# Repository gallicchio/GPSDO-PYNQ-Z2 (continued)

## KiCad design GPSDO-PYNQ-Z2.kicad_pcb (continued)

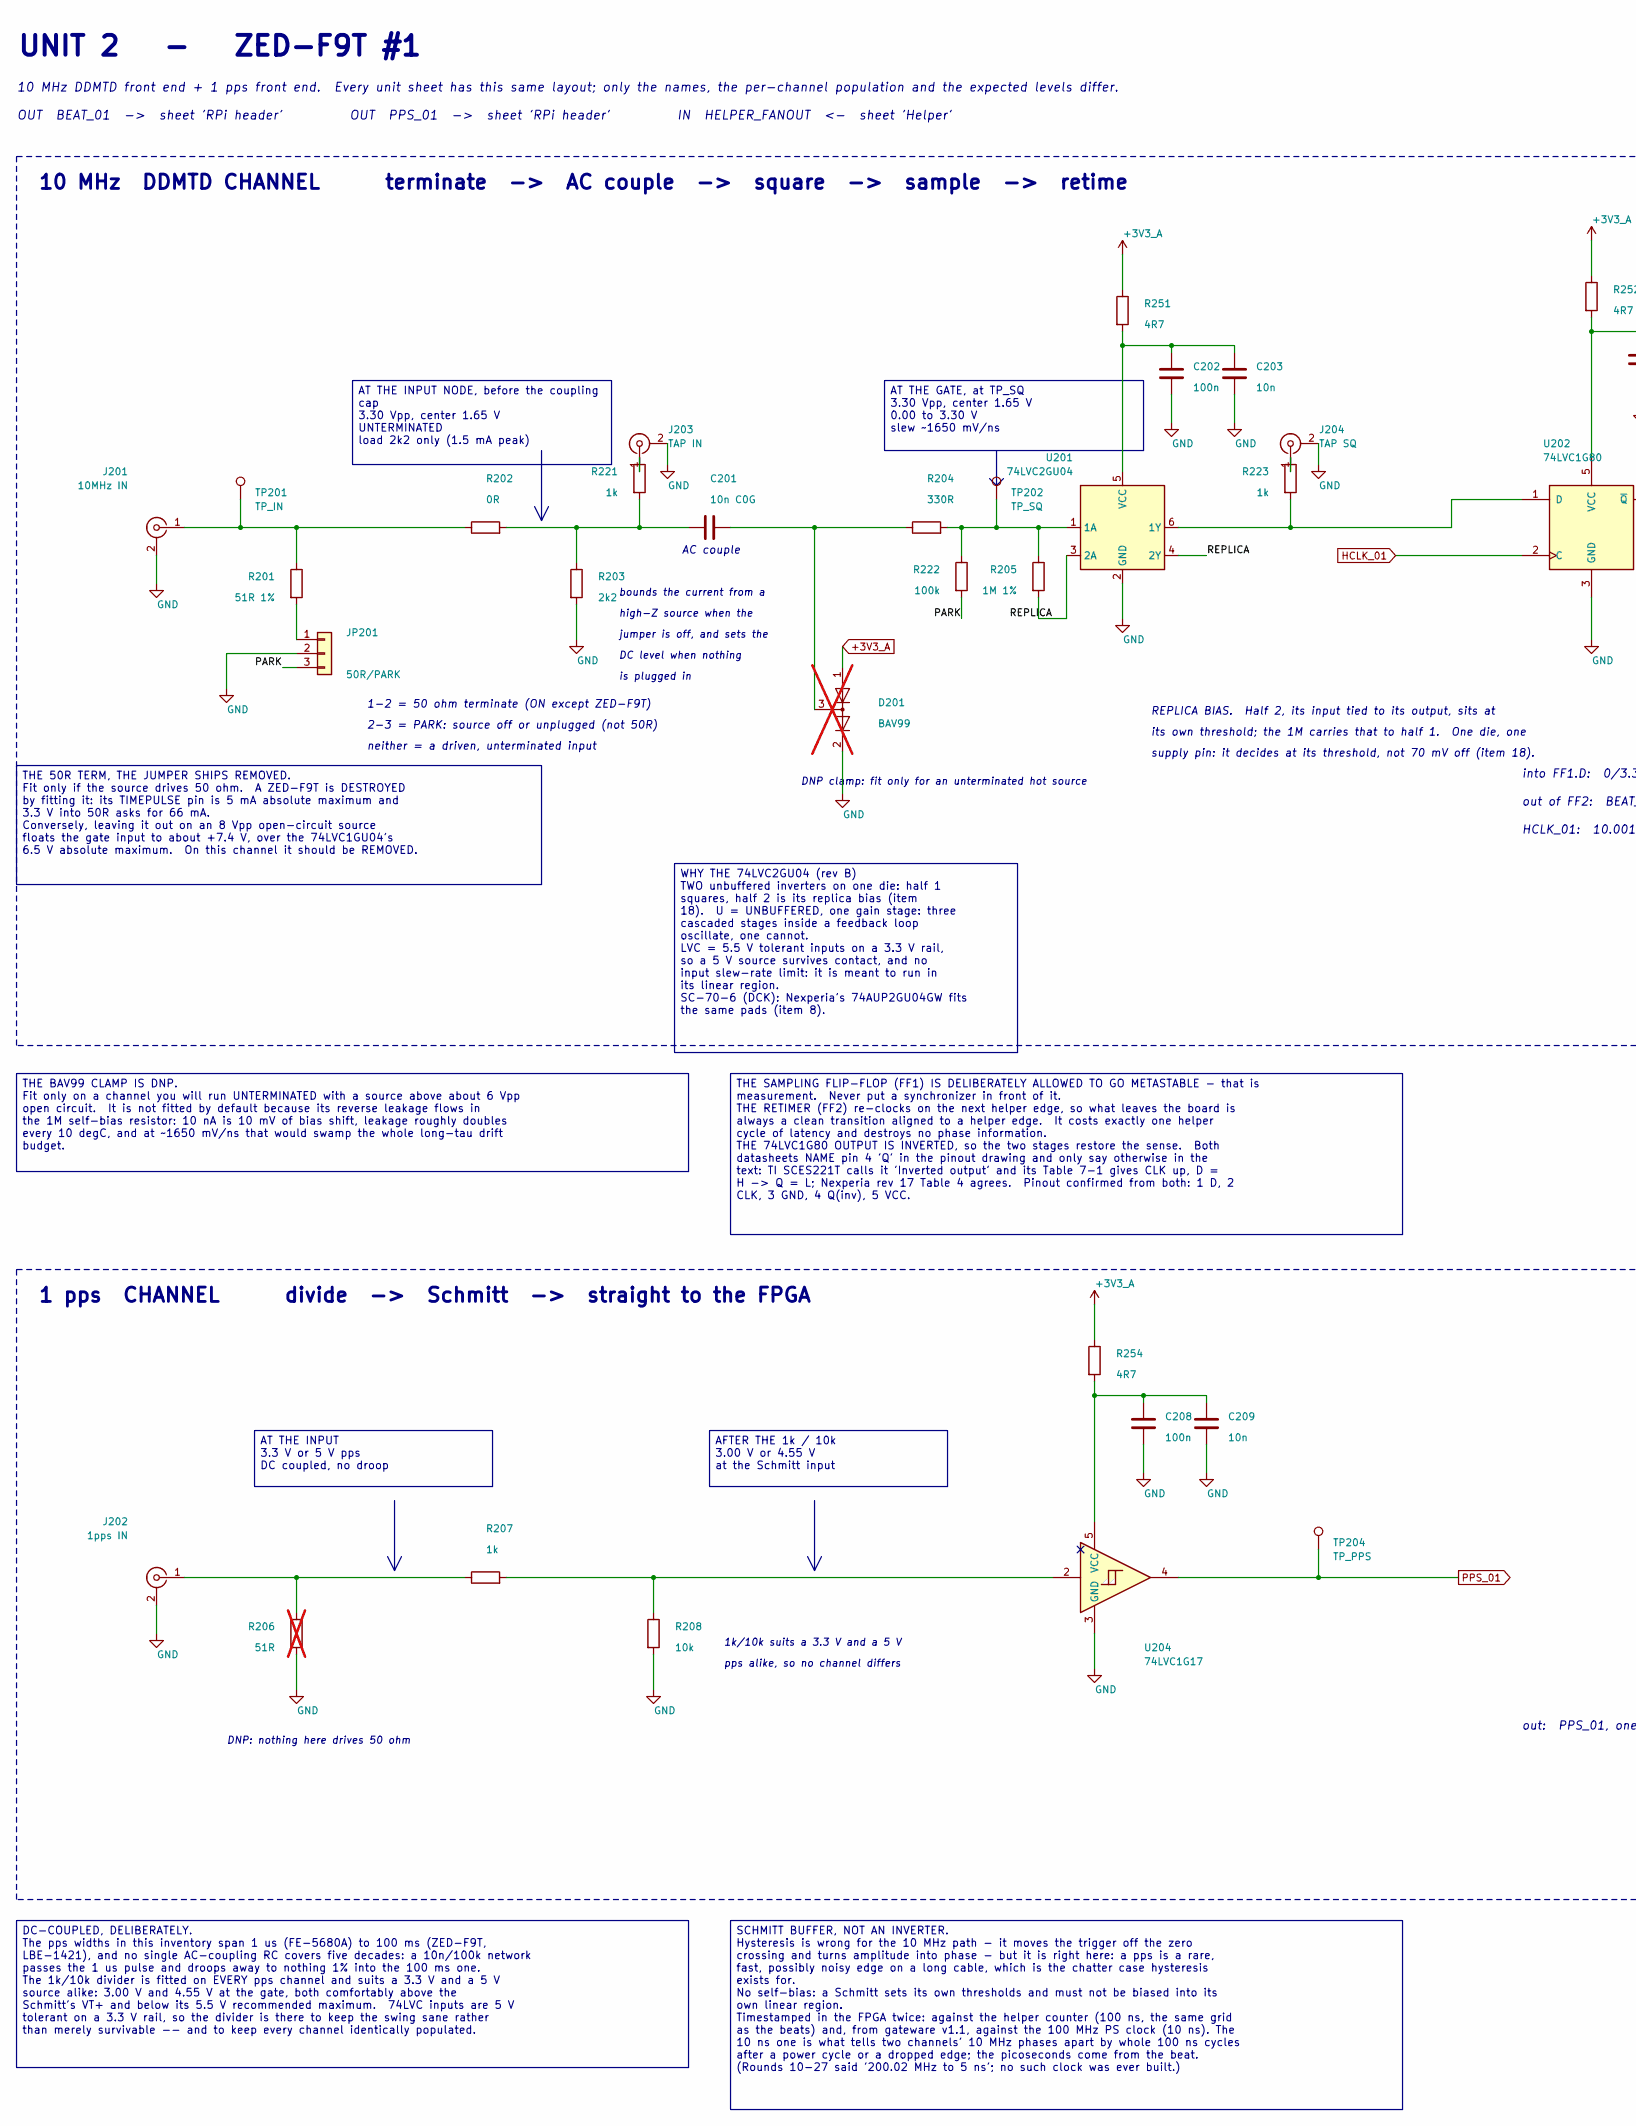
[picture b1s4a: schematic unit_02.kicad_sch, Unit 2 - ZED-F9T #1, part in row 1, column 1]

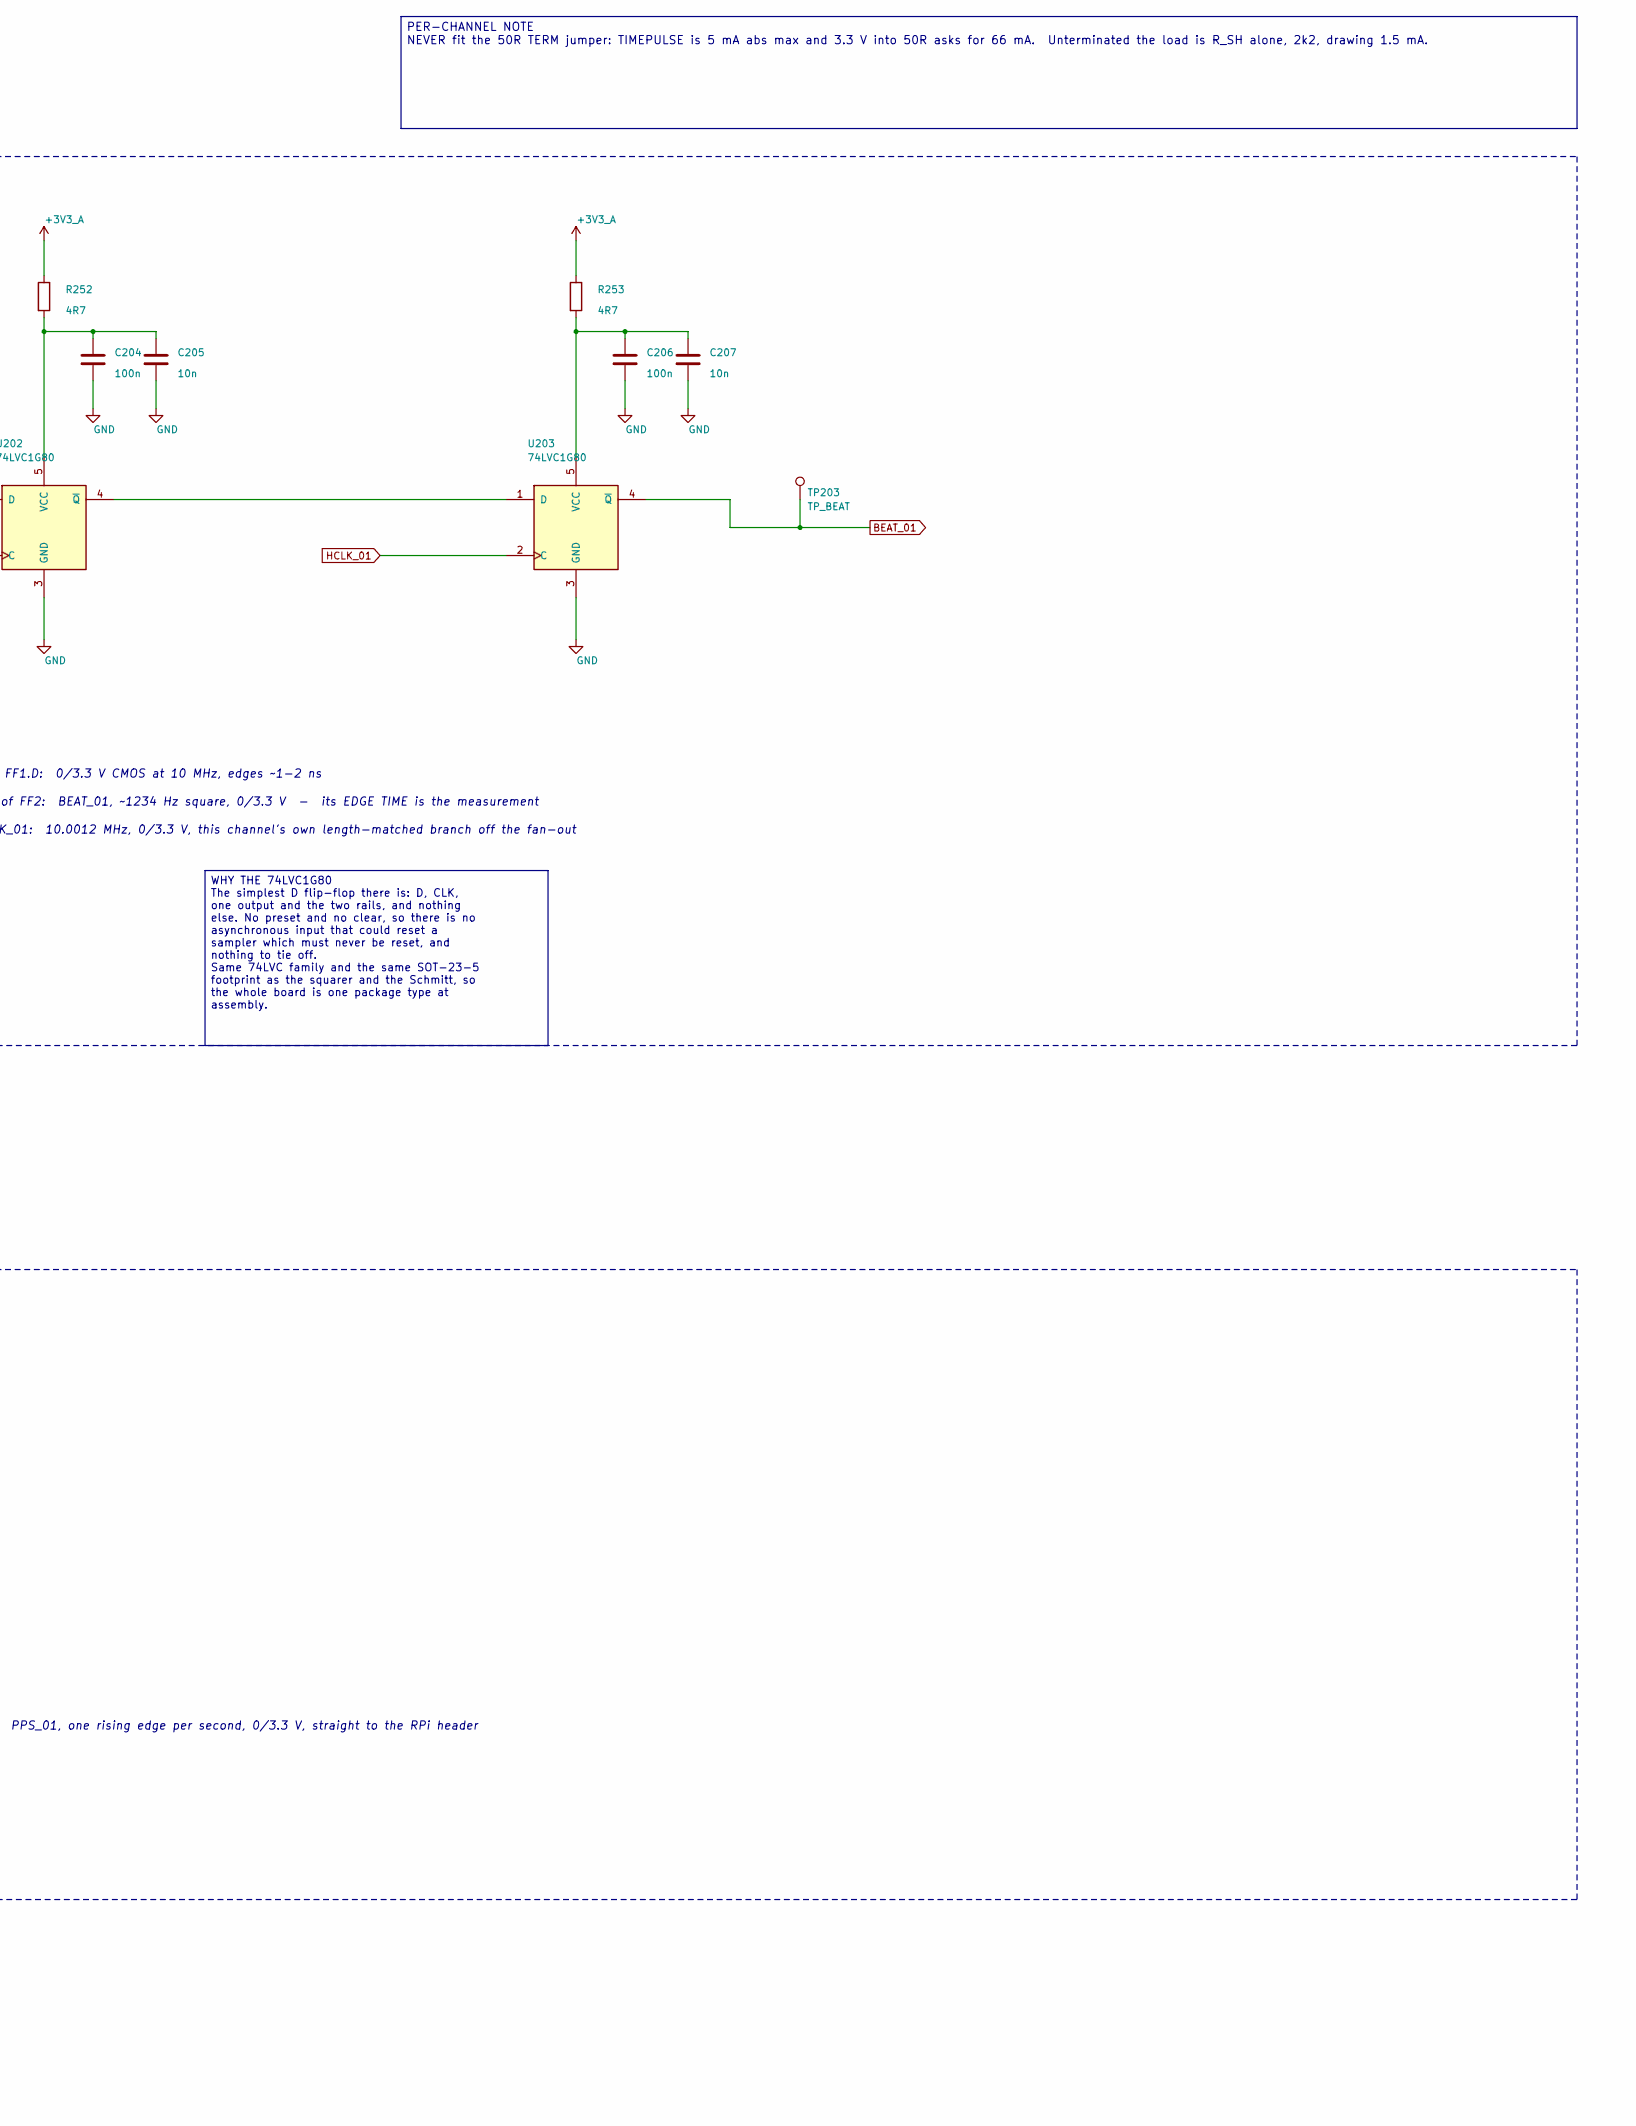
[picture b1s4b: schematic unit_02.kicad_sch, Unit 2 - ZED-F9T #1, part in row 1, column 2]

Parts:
C201: 10n C0G; C_0805_2012Metric
C202, C204, C206, C208: 100n; C_0805_2012Metric
C203, C205, C207, C209: 10n; C_0805_2012Metric
D201: BAV99; SOT-23; LCSC C916421; not fitted
J201: 10MHz IN; SMA_Vertical_THT_Universal; LCSC C496549
J202: 1pps IN; SMA_Vertical_THT_Universal; LCSC C496549
J203: TAP IN; U.FL_Hirose_U.FL-R-SMT-1_Vertical; LCSC C88374
J204: TAP SQ; U.FL_Hirose_U.FL-R-SMT-1_Vertical; LCSC C88374
JP201: 50R/PARK; PinHeader_1x03_P2.54mm_Vertical
R201: 51R 1%; R_0805_2012Metric
R202: 0R; R_0805_2012Metric
R203: 2k2; R_0805_2012Metric
R204: 330R; R_0805_2012Metric
R205: 1M 1%; R_0805_2012Metric
R206: 51R; R_0805_2012Metric; not fitted
R207, R221, R223: 1k; R_0805_2012Metric
R208: 10k; R_0805_2012Metric
R222: 100k; R_0805_2012Metric
R251, R252, R253, R254: 4R7; R_0805_2012Metric
TP201: TP_IN; TestPoint_Pad_D1.5mm
TP202: TP_SQ; TestPoint_Pad_D1.5mm
TP203: TP_BEAT; TestPoint_Pad_D1.5mm
TP204: TP_PPS; TestPoint_Pad_D1.5mm
U201: 74LVC2GU04; SOT-363_SC-70-6; LCSC C116660
U202, U203: 74LVC1G80; SOT-23-5; LCSC C42879
U204: 74LVC1G17; SOT-23-5; LCSC C7836

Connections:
+3V3_A: D201.1 (K), R251.1, R252.1, R253.1, R254.1; also elsewhere on the board
/Unit 02/PARK: JP201.3, R222.2
/Unit 02/REPLICA: R205.2, U201.3 (2A), U201.4 (2Y)
BEAT_01: TP203.1, U203.4 (~Q); also elsewhere on the board
GND: C202.2, C203.2, C204.2, C205.2, C206.2, C207.2, C208.2, C209.2, D201.2 (A), J201.2 (Ext), J202.2 (Ext), J203.2 (Ext), J204.2 (Ext), JP201.2, R203.2, R206.2, R208.2, U201.2 (GND), U202.3 (GND), U203.3 (GND), U204.3 (GND); also elsewhere on the board
HCLK_01: U202.2 (C), U203.2 (C); also elsewhere on the board
unnamed: C201.1, R202.2, R203.1, R221.2
unnamed: C201.2, D201.3 (K), R204.1
unnamed: J201.1 (In), R201.1, R202.1, TP201.1
unnamed: J202.1 (In), R206.1, R207.1
unnamed: J203.1 (In), R221.1
unnamed: J204.1 (In), R223.1
unnamed: JP201.1, R201.2
unnamed: R207.2, R208.1, U204.2
unnamed: R204.2, R205.1, R222.1, TP202.1, U201.1 (1A)
unnamed: R223.2, U201.6 (1Y), U202.1 (D)
unnamed: C202.1, C203.1, R251.2, U201.5 (VCC)
unnamed: C204.1, C205.1, R252.2, U202.5 (VCC)
unnamed: U202.4 (~Q), U203.1 (D)
unnamed: C206.1, C207.1, R253.2, U203.5 (VCC)
unnamed: C208.1, C209.1, R254.2, U204.5 (VCC)
PPS_01: TP204.1, U204.4; also elsewhere on the board

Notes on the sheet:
bounds the current from a
into FF1.D: 0/3.3 V CMOS at 10 MHz, edges ~1-2 ns
is plugged in
out: PPS_01, one rising edge per second, 0/3.3 V, straight to the RPi header
10 MHz DDMTD CHANNEL terminate -> AC couple -> square -> sample -> retime
DNP: nothing here drives 50 ohm
supply pin: it decides at its threshold, not 70 mV off (item 18).
10 MHz DDMTD front end + 1 pps front end. Every unit sheet has this same layout; only the names, the per-channel population and the expected levels differ.
DNP clamp: fit only for an unterminated hot source
HCLK_01: 10.0012 MHz, 0/3.3 V, this channel's own length-matched branch off the fan-out
REPLICA BIAS. Half 2, its input tied to its output, sits at
DC level when nothing
1 pps CHANNEL divide -> Schmitt -> straight to the FPGA
AC couple
1-2 = 50 ohm terminate (ON except ZED-F9T)
OUT BEAT_01 -> sheet 'RPi header' OUT PPS_01 -> sheet 'RPi header' IN HELPER_FANOUT <- sheet 'Helper'
UNIT 2 - ZED-F9T #1
high-Z source when the
1k/10k suits a 3.3 V and a 5 V
jumper is off, and sets the
2-3 = PARK: source off or unplugged (not 50R)
out of FF2: BEAT_01, ~1234 Hz square, 0/3.3 V - its EDGE TIME is the measurement
pps alike, so no channel differs
its own threshold; the 1M carries that to half 1. One die, one
neither = a driven, unterminated input
THE SAMPLING FLIP-FLOP (FF1) IS DELIBERATELY ALLOWED TO GO METASTABLE - that is measurement. Never put a synchronizer in front of it. THE RETIMER (FF2) re-clocks on the next helper edge, so what leaves the board is always a clean transition aligned to a helper edge. It costs exactly one helper cycl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
WHY THE 74LVC2GU04 (rev B) TWO unbuffered inverters on one die: half 1 squares, half 2 is its replica bias (item 18). U = UNBUFFERED, one gain stage: three cascaded stages inside a feedback loop oscillate, one cannot. LVC = 5.5 V tolerant inputs on a 3.3 V rail, so a 5 V source survives contact, an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
THE BAV99 CLAMP IS DNP. Fit only on a channel you will run UNTERMINATED with a source above about 6 Vpp open circuit. It is not fitted by default because its reverse leakage flows in the 1M self-bias resistor: 10 nA is 10 mV of bias shift, leakage roughly doubles every 10 degC, and at ~1650 mV/ns t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
AT THE INPUT 3.3 V or 5 V pps DC coupled, no droop
AFTER THE 1k / 10k 3.00 V or 4.55 V at the Schmitt input
AT THE GATE, at TP_SQ 3.30 Vpp, center 1.65 V 0.00 to 3.30 V slew ~1650 mV/ns
WHY THE 74LVC1G80 The simplest D flip-flop there is: D, CLK, one output and the two rails, and nothing else. No preset and no clear, so there is no asynchronous input that could reset a sampler which must never be reset, and nothing to tie off. Same 74LVC family and the same SOT-23-5 footprint as t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
THE 50R TERM, THE JUMPER SHIPS REMOVED. Fit only if the source drives 50 ohm. A ZED-F9T is DESTROYED by fitting it: its TIMEPULSE pin is 5 mA absolute maximum and 3.3 V into 50R asks for 66 mA. Conversely, leaving it out on an 8 Vpp open-circuit source floats the gate input to about +7.4 V, over th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
AT THE INPUT NODE, before the coupling cap 3.30 Vpp, center 1.65 V UNTERMINATED load 2k2 only (1.5 mA peak)
PER-CHANNEL NOTE NEVER fit the 50R TERM jumper: TIMEPULSE is 5 mA abs max and 3.3 V into 50R asks for 66 mA. Unterminated the load is R_SH alone, 2k2, drawing 1.5 mA.
DC-COUPLED, DELIBERATELY. The pps widths in this inventory span 1 us (FE-5680A) to 100 ms (ZED-F9T, LBE-1421), and no single AC-coupling RC covers five decades: a 10n/100k network passes the 1 us pulse and droops away to nothing 1% into the 100 ms one. The 1k/10k divider is fitted on EVERY pps chan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
SCHMITT BUFFER, NOT AN INVERTER. Hysteresis is wrong for the 10 MHz path - it moves the trigger off the zero crossing and turns amplitude into phase - but it is right here: a pps is a rare, fast, possibly noisy edge on a long cable, which is the chatter case hysteresis exists for. No self-bias: a S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

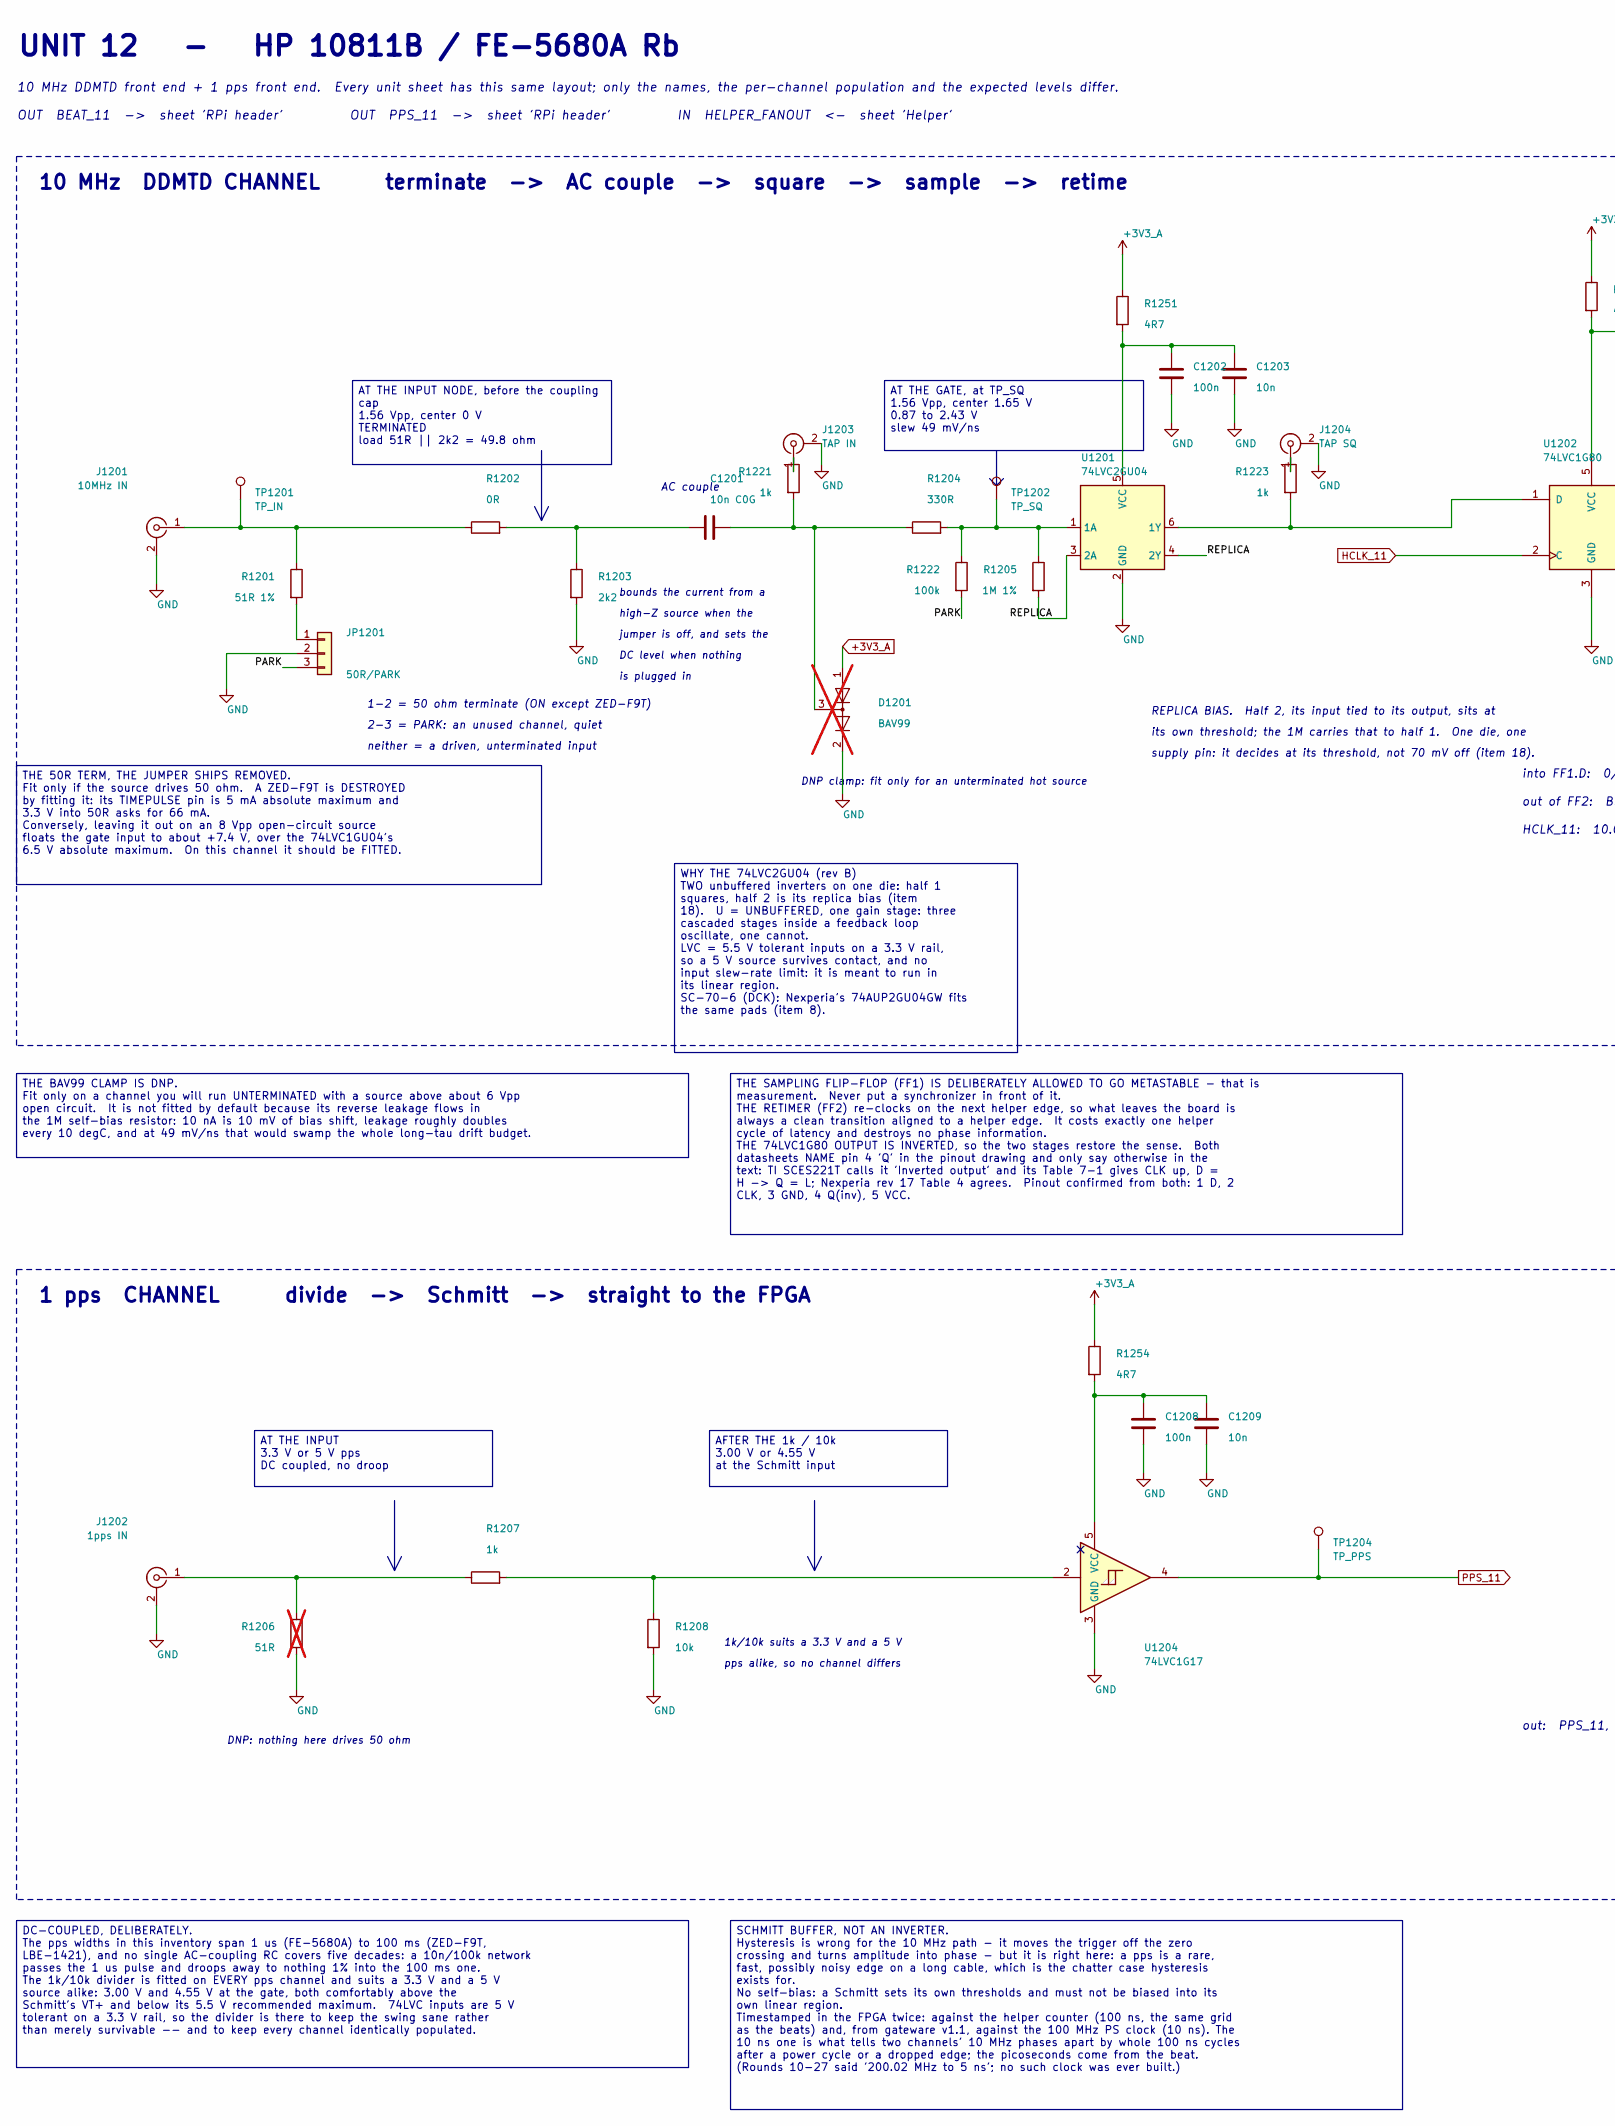
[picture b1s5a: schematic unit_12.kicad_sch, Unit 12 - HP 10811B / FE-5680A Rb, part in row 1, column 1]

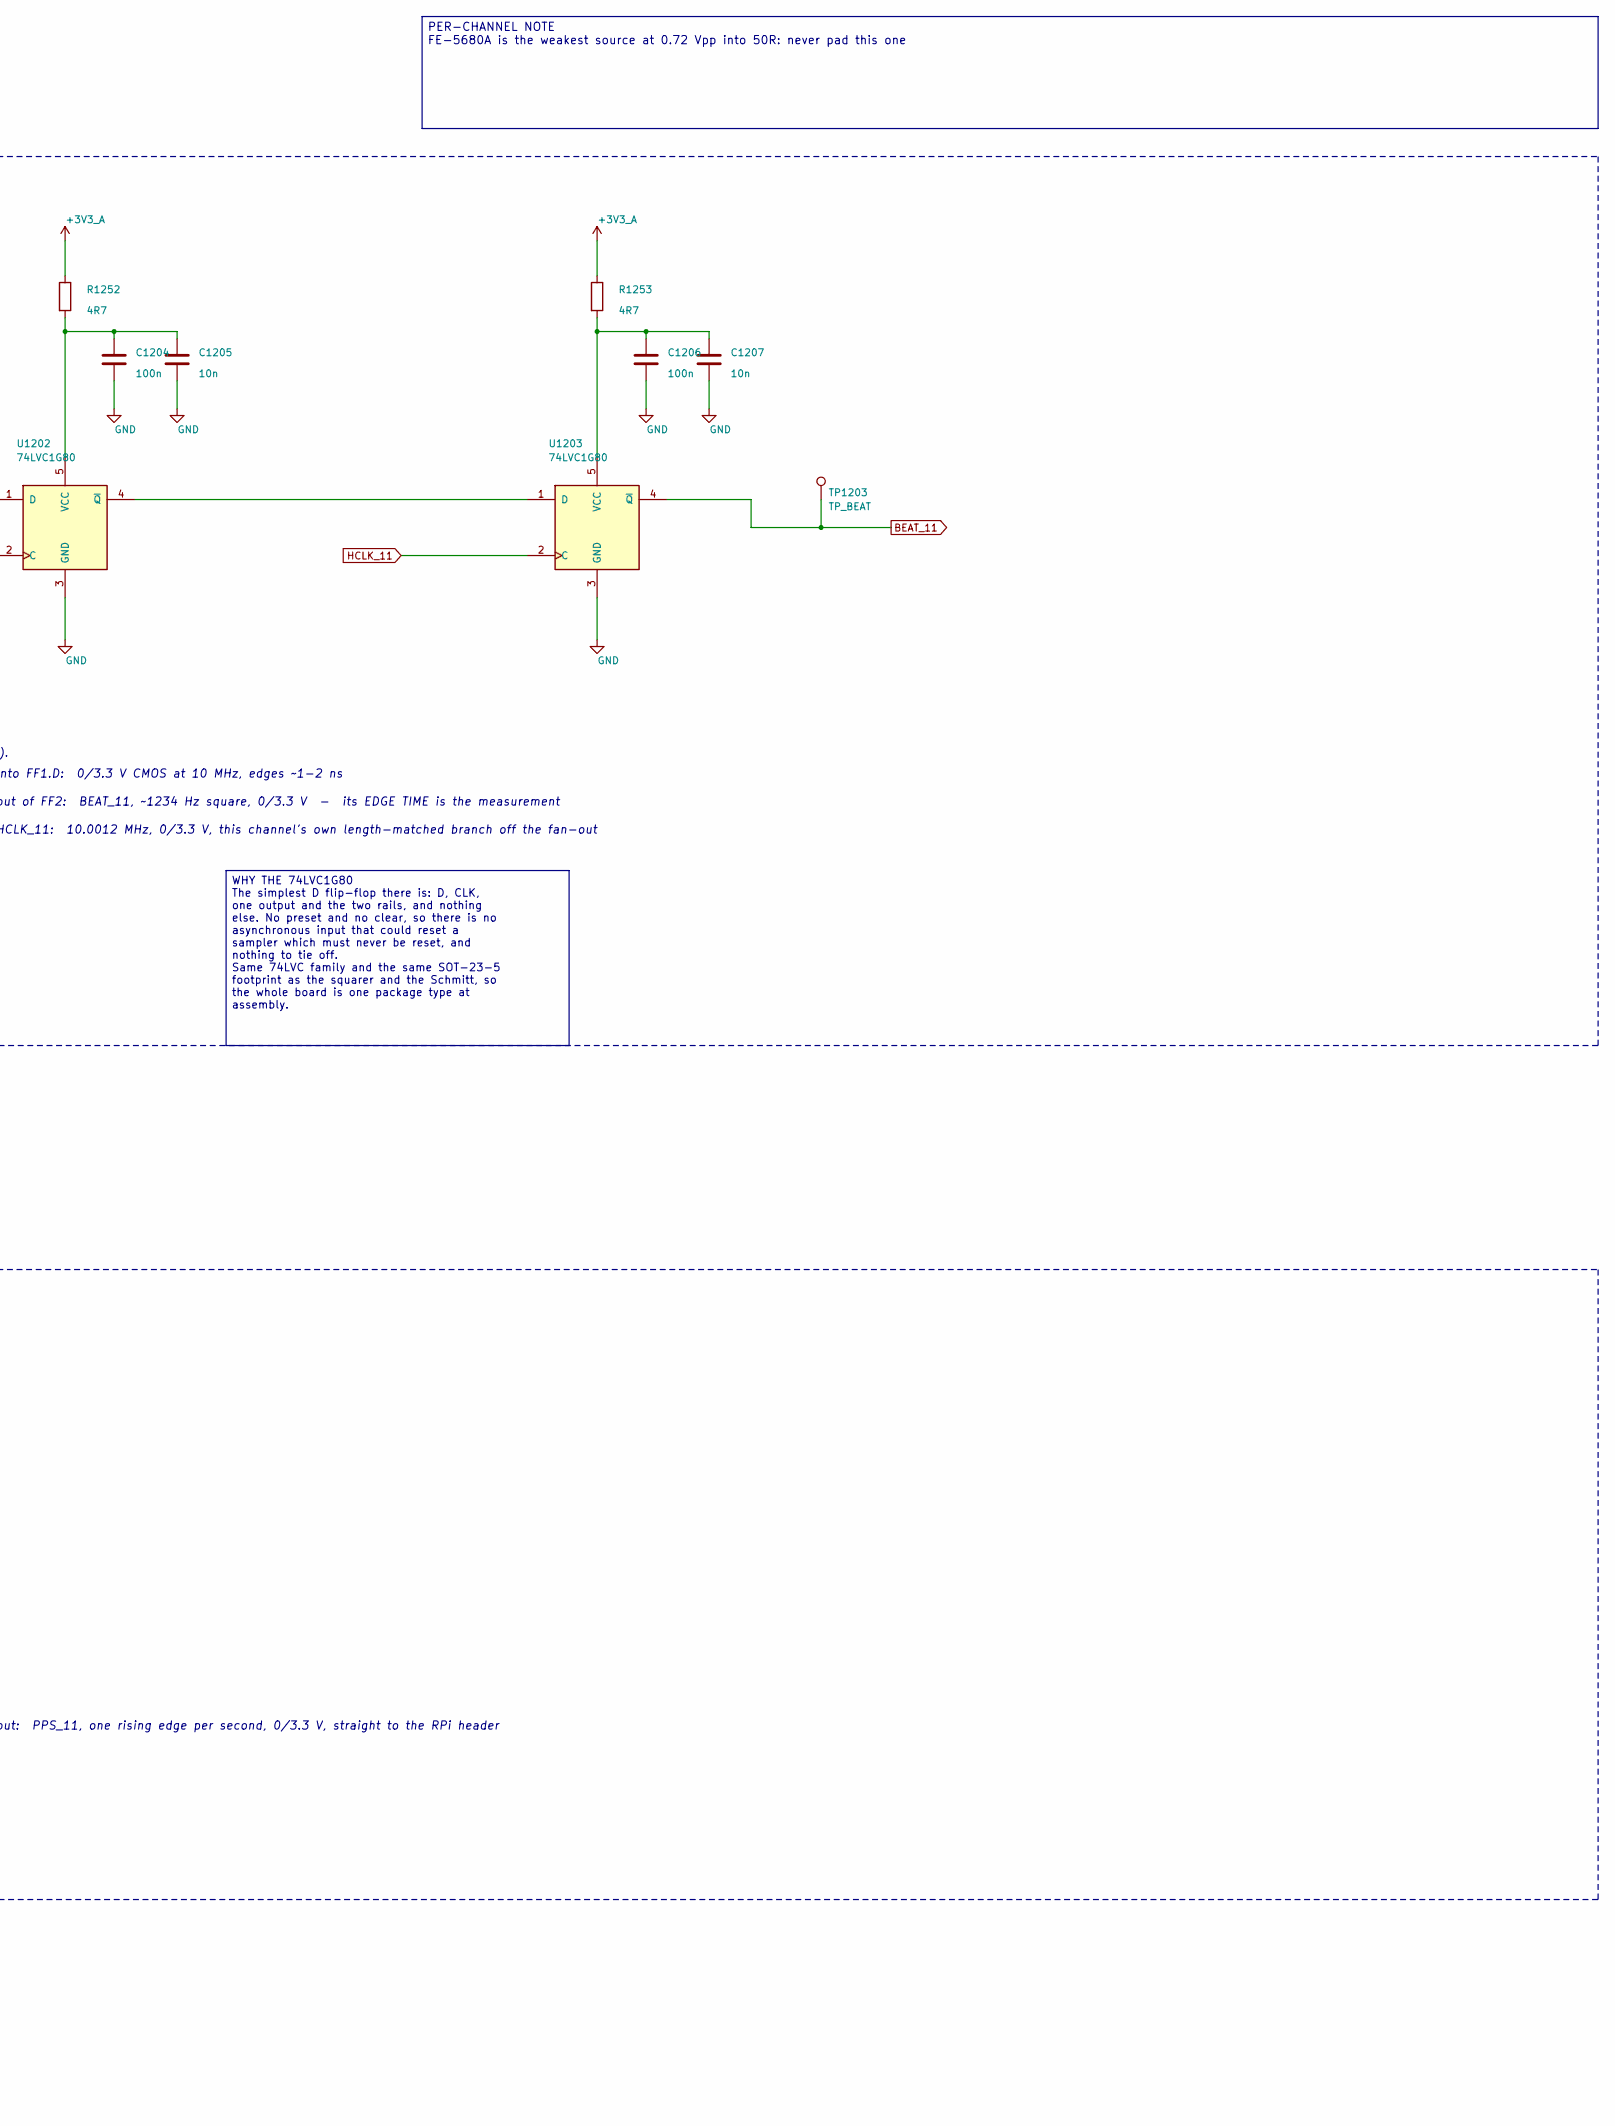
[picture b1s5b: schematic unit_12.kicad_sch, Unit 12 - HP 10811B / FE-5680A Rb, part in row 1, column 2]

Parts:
C1201: 10n C0G; C_0805_2012Metric
C1202, C1204, C1206, C1208: 100n; C_0805_2012Metric
C1203, C1205, C1207, C1209: 10n; C_0805_2012Metric
D1201: BAV99; SOT-23; LCSC C916421; not fitted
J1201: 10MHz IN; SMA_Vertical_THT_Universal; LCSC C496549
J1202: 1pps IN; SMA_Vertical_THT_Universal; LCSC C496549
J1203: TAP IN; U.FL_Hirose_U.FL-R-SMT-1_Vertical; LCSC C88374
J1204: TAP SQ; U.FL_Hirose_U.FL-R-SMT-1_Vertical; LCSC C88374
JP1201: 50R/PARK; PinHeader_1x03_P2.54mm_Vertical
R1201: 51R 1%; R_0805_2012Metric
R1202: 0R; R_0805_2012Metric
R1203: 2k2; R_0805_2012Metric
R1204: 330R; R_0805_2012Metric
R1205: 1M 1%; R_0805_2012Metric
R1206: 51R; R_0805_2012Metric; not fitted
R1207, R1221, R1223: 1k; R_0805_2012Metric
R1208: 10k; R_0805_2012Metric
R1222: 100k; R_0805_2012Metric
R1251, R1252, R1253, R1254: 4R7; R_0805_2012Metric
TP1201: TP_IN; TestPoint_Pad_D1.5mm
TP1202: TP_SQ; TestPoint_Pad_D1.5mm
TP1203: TP_BEAT; TestPoint_Pad_D1.5mm
TP1204: TP_PPS; TestPoint_Pad_D1.5mm
U1201: 74LVC2GU04; SOT-363_SC-70-6; LCSC C116660
U1202, U1203: 74LVC1G80; SOT-23-5; LCSC C42879
U1204: 74LVC1G17; SOT-23-5; LCSC C7836

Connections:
+3V3_A: D1201.1 (K), R1251.1, R1252.1, R1253.1, R1254.1; also elsewhere on the board
/Unit 12/PARK: JP1201.3, R1222.2
/Unit 12/REPLICA: R1205.2, U1201.3 (2A), U1201.4 (2Y)
BEAT_11: TP1203.1, U1203.4 (~Q); also elsewhere on the board
GND: C1202.2, C1203.2, C1204.2, C1205.2, C1206.2, C1207.2, C1208.2, C1209.2, D1201.2 (A), J1201.2 (Ext), J1202.2 (Ext), J1203.2 (Ext), J1204.2 (Ext), JP1201.2, R1203.2, R1206.2, R1208.2, U1201.2 (GND), U1202.3 (GND), U1203.3 (GND), U1204.3 (GND); also elsewhere on the board
HCLK_11: U1202.2 (C), U1203.2 (C); also elsewhere on the board
unnamed: J1201.1 (In), R1201.1, R1202.1, TP1201.1
unnamed: J1202.1 (In), R1206.1, R1207.1
unnamed: J1203.1 (In), R1221.1
unnamed: J1204.1 (In), R1223.1
unnamed: JP1201.1, R1201.2
unnamed: R1207.2, R1208.1, U1204.2
unnamed: R1204.2, R1205.1, R1222.1, TP1202.1, U1201.1 (1A)
unnamed: R1223.2, U1201.6 (1Y), U1202.1 (D)
unnamed: C1202.1, C1203.1, R1251.2, U1201.5 (VCC)
unnamed: C1204.1, C1205.1, R1252.2, U1202.5 (VCC)
unnamed: U1202.4 (~Q), U1203.1 (D)
unnamed: C1206.1, C1207.1, R1253.2, U1203.5 (VCC)
unnamed: C1208.1, C1209.1, R1254.2, U1204.5 (VCC)
PPS_11: TP1204.1, U1204.4; also elsewhere on the board

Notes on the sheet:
pps alike, so no channel differs
DNP: nothing here drives 50 ohm
into FF1.D: 0/3.3 V CMOS at 10 MHz, edges ~1-2 ns
10 MHz DDMTD front end + 1 pps front end. Every unit sheet has this same layout; only the names, the per-channel population and the expected levels differ.
out: PPS_11, one rising edge per second, 0/3.3 V, straight to the RPi header
supply pin: it decides at its threshold, not 70 mV off (item 18).
1 pps CHANNEL divide -> Schmitt -> straight to the FPGA
2-3 = PARK: an unused channel, quiet
jumper is off, and sets the
1-2 = 50 ohm terminate (ON except ZED-F9T)
HCLK_11: 10.0012 MHz, 0/3.3 V, this channel's own length-matched branch off the fan-out
out of FF2: BEAT_11, ~1234 Hz square, 0/3.3 V - its EDGE TIME is the measurement
REPLICA BIAS. Half 2, its input tied to its output, sits at
DC level when nothing
10 MHz DDMTD CHANNEL terminate -> AC couple -> square -> sample -> retime
neither = a driven, unterminated input
is plugged in
DNP clamp: fit only for an unterminated hot source
UNIT 12 - HP 10811B / FE-5680A Rb
OUT BEAT_11 -> sheet 'RPi header' OUT PPS_11 -> sheet 'RPi header' IN HELPER_FANOUT <- sheet 'Helper'
bounds the current from a
its own threshold; the 1M carries that to half 1. One die, one
high-Z source when the
1k/10k suits a 3.3 V and a 5 V
AC couple
WHY THE 74LVC1G80 The simplest D flip-flop there is: D, CLK, one output and the two rails, and nothing else. No preset and no clear, so there is no asynchronous input that could reset a sampler which must never be reset, and nothing to tie off. Same 74LVC family and the same SOT-23-5 footprint as t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
DC-COUPLED, DELIBERATELY. The pps widths in this inventory span 1 us (FE-5680A) to 100 ms (ZED-F9T, LBE-1421), and no single AC-coupling RC covers five decades: a 10n/100k network passes the 1 us pulse and droops away to nothing 1% into the 100 ms one. The 1k/10k divider is fitted on EVERY pps chan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
PER-CHANNEL NOTE FE-5680A is the weakest source at 0.72 Vpp into 50R: never pad this one
AT THE GATE, at TP_SQ 1.56 Vpp, center 1.65 V 0.87 to 2.43 V slew 49 mV/ns
AT THE INPUT 3.3 V or 5 V pps DC coupled, no droop
THE 50R TERM, THE JUMPER SHIPS REMOVED. Fit only if the source drives 50 ohm. A ZED-F9T is DESTROYED by fitting it: its TIMEPULSE pin is 5 mA absolute maximum and 3.3 V into 50R asks for 66 mA. Conversely, leaving it out on an 8 Vpp open-circuit source floats the gate input to about +7.4 V, over th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
THE BAV99 CLAMP IS DNP. Fit only on a channel you will run UNTERMINATED with a source above about 6 Vpp open circuit. It is not fitted by default because its reverse leakage flows in the 1M self-bias resistor: 10 nA is 10 mV of bias shift, leakage roughly doubles every 10 degC, and at 49 mV/ns that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
SCHMITT BUFFER, NOT AN INVERTER. Hysteresis is wrong for the 10 MHz path - it moves the trigger off the zero crossing and turns amplitude into phase - but it is right here: a pps is a rare, fast, possibly noisy edge on a long cable, which is the chatter case hysteresis exists for. No self-bias: a S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
AFTER THE 1k / 10k 3.00 V or 4.55 V at the Schmitt input
WHY THE 74LVC2GU04 (rev B) TWO unbuffered inverters on one die: half 1 squares, half 2 is its replica bias (item 18). U = UNBUFFERED, one gain stage: three cascaded stages inside a feedback loop oscillate, one cannot. LVC = 5.5 V tolerant inputs on a 3.3 V rail, so a 5 V source survives contact, an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
AT THE INPUT NODE, before the coupling cap 1.56 Vpp, center 0 V TERMINATED load 51R || 2k2 = 49.8 ohm
THE SAMPLING FLIP-FLOP (FF1) IS DELIBERATELY ALLOWED TO GO METASTABLE - that is measurement. Never put a synchronizer in front of it. THE RETIMER (FF2) re-clocks on the next helper edge, so what leaves the board is always a clean transition aligned to a helper edge. It costs exactly one helper cycl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
